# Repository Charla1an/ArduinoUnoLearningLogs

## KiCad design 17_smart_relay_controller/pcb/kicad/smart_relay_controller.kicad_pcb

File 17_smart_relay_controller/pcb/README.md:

# Smart Relay Controller – PCB (KiCad)

This folder documents the PCB version of Project 17, the [Smart Relay Controller](../README.md). It is the first PCB I have designed, and the first one in this log.

The main README covers the breadboard project: how it works, the concepts involved, and the challenges I ran into. This file only covers the PCB: what I designed, how I designed it, what went wrong along the way, and what has and has not been checked.

## Status

| Stage | Status |
|---|---|
| Schematic completed | Yes |
| Schematic ERC | Checked, passes |
| PCB layout designed | Yes |
| PCB DRC | Checked: 0 errors, 0 unconnected items, 0 warnings |
| 3D fit check | Done: components fit on the board (relay shown with a stand-in 3D model) |
| Footprints vs datasheets | Done: every component matches (not checked against physical parts) |
| Gerber / drill files generated | No |
| Fabricated | **No** (design only) |
| Assembled | **No** |
| Physically tested | **No** |

**In short: designed in KiCad and checked with ERC, DRC, a 3D fit check and a datasheet check of every footprint. Not fabricated, assembled or tested, and I am not going to fabricate it.** These are checks on the design. They do not show that a fabricated board would work.

## Why I Made It

My main reason was to learn more about PCB design, and the best way to do that seemed to be designing boards for circuits I am already familiar with. Project 17 was already built on a breadboard, so the new part was the PCB process: schematic, footprints, layout, and the checks in between. It also took the circuit one step past the breadboard. I am designing the board, not fabricating it.

## What's on the Board

Resistor values were taken from the breadboard circuit, not redesigned for the PCB.

| Ref | Part | KiCad footprint |
|---|---|---|
| A2 | Arduino Nano V3.x | `Module:Arduino_Nano` |
| D1 | 1N4001 (flyback diode) | `Diode_THT:D_DO-41_SOD81_P10.16mm_Horizontal` |
| D2 | LED | `LED_THT:LED_D3.0mm_FlatTop` |
| K1 | JQC-3FC(T73) DC 5 V relay (SPDT) | `Relay_THT:Relay_SPDT_Hongfa_JQC-3FF_0XX-1Z` |
| Q1 | S8050 NPN transistor | `Package_TO_SOT_THT:TO-92_Inline` |
| R1 | 220 Ω | `Resistor_THT:R_Axial_DIN0207_L6.3mm_D2.5mm_P7.62mm_Horizontal` |
| R2 | 1 kΩ | `Resistor_THT:R_Axial_DIN0207_L6.3mm_D2.5mm_P7.62mm_Horizontal` |
| SW1 | Pushbutton | `Button_Switch_THT:SW_PUSH_6mm_H4.3mm` |

Connections as drawn in the schematic:

- D5 → SW1 → GND (the button is meant to use the Arduino's internal pull-up)
- D9 → R2 → Q1 base; Q1 emitter → GND; Q1 collector → K1 coil (low side)
- K1 coil (other side) → +5 V, with D1 across the coil for flyback protection
- K1 contacts: COM (11) → +5 V, NO (14) → R1 → D2 → GND side; NC (12) unused
- The Arduino and the switching circuit share one +5 V net and one GND net

The full-resolution schematic is in [`docs/schematic.pdf`](docs/schematic.pdf).

## Workflow

Schematic → ERC → footprint assignment → PCB layout → placement → routing → GND copper zone → DRC → 3D inspection.

I finished the schematic before starting the layout.

## Design Decisions

**Uno R3 → Nano V3.x.** The breadboard version uses an Arduino Uno R3, and the PCB started out with an Uno R3 symbol and footprint. During the final design I replaced it with an Arduino Nano V3.x symbol and footprint (`Module:Arduino_Nano`) in both the schematic and the PCB. I did it for convenience for whoever fabricates the board: the Nano has male pins, unlike the Uno's female headers, so it can be placed directly on the PCB. The connections the circuit uses (D5, D9, +5 V, GND) stay the same.

The intended arrangement is to place the Nano directly on the board through its pins. Nothing has been built, so this has not been tested.

**Two layers, GND as a copper zone.** The board has two copper layers. F.Cu carries the +5 V copper, and B.Cu is a GND copper zone. I used a zone for GND instead of routing one large GND trace by hand. The other connections were routed manually.

**Resistor values kept.** R1 (220 Ω) and R2 (1 kΩ) come from the physical Project 17 circuit. I did not recalculate them for the PCB.

**Relay footprint.** The footprint library name (`Relay_SPDT_Hongfa_JQC-3FF_0XX-1Z`) does not match the physical relay I have, which is a JQC-3FC(T73) DC 5 V. I picked it because its pad arrangement corresponded to the arrangement of my relay. A different name does not make a footprint wrong, but its geometry has to match the real part. I checked the footprint against the JQC-3FC datasheet (hole spacing, body outline, drill sizes and pad numbering) and it matches (see Verification).

**S8050 footprint.** I used `TO-92_Inline`. The symbol and footprint pin numbering correspond in KiCad, and I checked the S8050's pin order against its datasheet, which matches.

## Board

- KiCad 10.0
- 2 copper layers: F.Cu (+5 V copper), B.Cu (GND zone)
- Rounded rectangular outline, approximately 45.3 mm × 45.2 mm (X 172.5 → 217.8 mm, Y 75.6 → 120.8 mm in KiCad's coordinates)

I have not recorded trace width, clearance or board thickness for this board, so I am not listing them.

*The relay in this render is a stand-in 3D model of the 3F version, because I could not find a model for the JQC-3FC(T73).*

## Verification

**ERC (schematic):** passes after the fixes described under Challenges.

**DRC (PCB), final result:**

- Errors: 0
- Unconnected items: 0
- Warnings: 0

DRC checks the layout against KiCad's rules. It does not check that the footprints match the real parts, and it says nothing about how a fabricated board would behave.

**3D inspection:** I used KiCad's 3D viewer to check that the components fit on the board. I could not find a 3D model for the JQC-3FC(T73), so the relay in the render is a model of the 3F version, which has essentially the same dimensions. This is a visual fit check against that stand-in model. The relay footprint itself was checked separately against its datasheet (below).

**Footprints against datasheets:** I checked every component's footprint against its datasheet, and everything matched:

- Relay (JQC-3FC): hole spacing, body outline, drill sizes and pad numbering
- S8050: pin order against the symbol
- D1 and D2: polarity
- Pushbutton: pin pairs
- Nano: footprint and the D5, D9, +5 V and GND pins

These are checks against datasheets and the footprints, not against built hardware.

## Challenges

**ERC power errors.** The first ERC runs failed on power-related problems:

1. I had put a `PWR_FLAG` on the +5 V net. That caused a power-output conflict, because the Arduino symbol already defines its +5 V pin as a power output. I removed the +5 V `PWR_FLAG`.
2. The GND net did need a `PWR_FLAG` for ERC to pass, so I added one.
3. The Arduino's GND pins were treated as unused. I connected them to GND.
4. Unused Arduino pins got No Connect markers.

After these fixes the schematic passed ERC.

**Silkscreen warnings.** DRC reported "Silkscreen clipped by board edge" warnings. They were cosmetic, and I cleared them, so the final DRC has no warnings.

**Layout.** Once the schematic and footprints were sorted out, the layout was relatively straightforward, and easier than I expected. I did not run into major placement, routing or 3D-check problems.

## Not Verified

- The footprints were checked against datasheets, not against the physical parts, because nothing has been built.
- No board has been fabricated, so nothing has been fitted, soldered, powered or tested. That includes the Nano on its footprint and the relay actually switching on this board.
- Gerber and drill files have not been generated.

## Files

| File | What it is |
|---|---|
| [`kicad/smart_relay_controller.kicad_pro`](kicad/smart_relay_controller.kicad_pro) | KiCad project |
| [`kicad/smart_relay_controller.kicad_sch`](kicad/smart_relay_controller.kicad_sch) | Schematic |
| [`kicad/smart_relay_controller.kicad_pcb`](kicad/smart_relay_controller.kicad_pcb) | PCB layout |
| [`docs/schematic.pdf`](docs/schematic.pdf) | Schematic export |
| [`docs/schematic.png`](docs/schematic.png) | Schematic image |
| [`docs/pcb-layout.png`](docs/pcb-layout.png) | PCB layout image |
| [`docs/pcb-3d-render.png`](docs/pcb-3d-render.png) | 3D render |
| [`docs/drc-result.png`](docs/drc-result.png) | DRC result screenshot |

Gerber and drill files have not been generated yet.

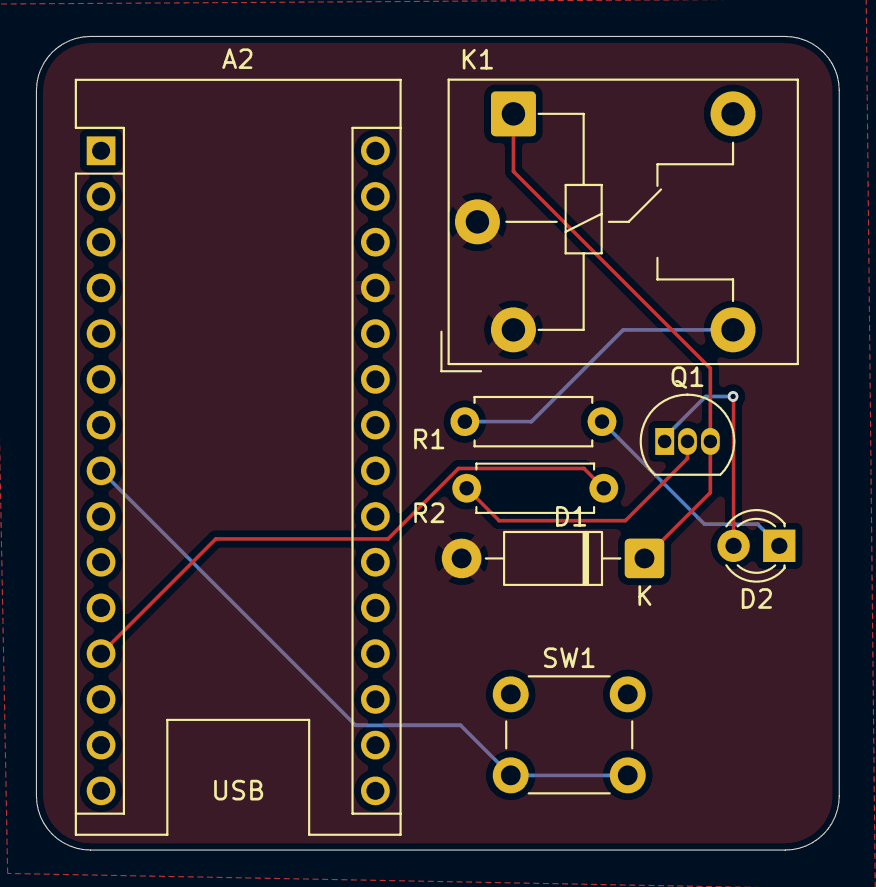
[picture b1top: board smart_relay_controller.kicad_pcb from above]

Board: 2 copper layers, 44.6 x 45.2 mm, 8 parts (0 on the bottom side), 8 nets.

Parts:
A2: Arduino_Nano_v3.x; Arduino_Nano
D1: 1N4001; D_DO-41_SOD81_P10.16mm_Horizontal
D2: LED_Small_Filled; LED_D3.0mm_FlatTop
K1: Relay_SPDT; Relay_SPDT_Hongfa_JQC-3FF_0XX-1Z
Q1: S8050; TO-92_Inline
R1: 220; R_Axial_DIN0207_L6.3mm_D2.5mm_P7.62mm_Horizontal
R2: 1k; R_Axial_DIN0207_L6.3mm_D2.5mm_P7.62mm_Horizontal
SW1: SW_Push; SW_PUSH_6mm_H4.3mm

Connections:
+5V: A2.27 (+5V), D1.2 (A), K1.11, K1.A2
GND: A2.4 (GND), A2.29 (GND), D2.2 (A), Q1.1 (E), SW1.1
unnamed: A2.8 (D5), SW1.2
unnamed: A2.12 (D9), R2.2
unnamed: D1.1 (K), K1.A1, Q1.3 (C)
unnamed: D2.1 (K), R1.2
unnamed: K1.14, R1.1
unnamed: Q1.2 (B), R2.1

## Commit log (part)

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2026-05-04 Add README for LED brightness fader project
    Added README.md to explain the LED brightness fader project, including components, functionality, challenges, and future improvements.
2026-05-04 Add potentiometer brightness controller code
2026-05-04 Changed name of folder
2026-05-04 Create README for Potentiometer Brightness Control project
    Added a README file explaining the project, components, functionality, challenges, and learnings.
2026-05-07 Add basic on-off button control functionality
2026-05-07 Add toggle button functionality in toggleButton.ino
2026-05-08 name changes
2026-05-09 Implement RGB intensity control with buttons and potentiometer
2026-05-15 Add reaction time game code in Arduino
2026-05-15 Implement multi-mode traffic signal logic
2026-05-15 Add RGB control system with serial input
2026-05-15 Added LED animation control with button inputs
2026-05-17 Add light reactive lamp functionality in code.ino
2026-05-18 Implement temperature warning system with RGB LED
2026-05-20 Add README for Reaction Timer Game
    Added README.md for the Reaction Timer Game, detailing its features, components, concepts learned, challenges faced, and future improvements.
2026-05-20 Add README for Light-Reactive Smart Lamp project
    Added detailed README for the Light-Reactive Smart Lamp project, outlining its features, components, concepts learned, challenges faced, and future improvements.
2026-05-24 Added code for ultrasonic parking assistant
2026-06-05 Added code for Ultrasonic Object Locator
2026-06-05 Created README file for project 14
2026-06-13 Added code.ino for project 15
2026-06-13 Added README file for Single-Digit 7-Segment Display Counter
2026-06-15 Added code for which number is greater game
2026-06-15 Added README for which number is greater game
